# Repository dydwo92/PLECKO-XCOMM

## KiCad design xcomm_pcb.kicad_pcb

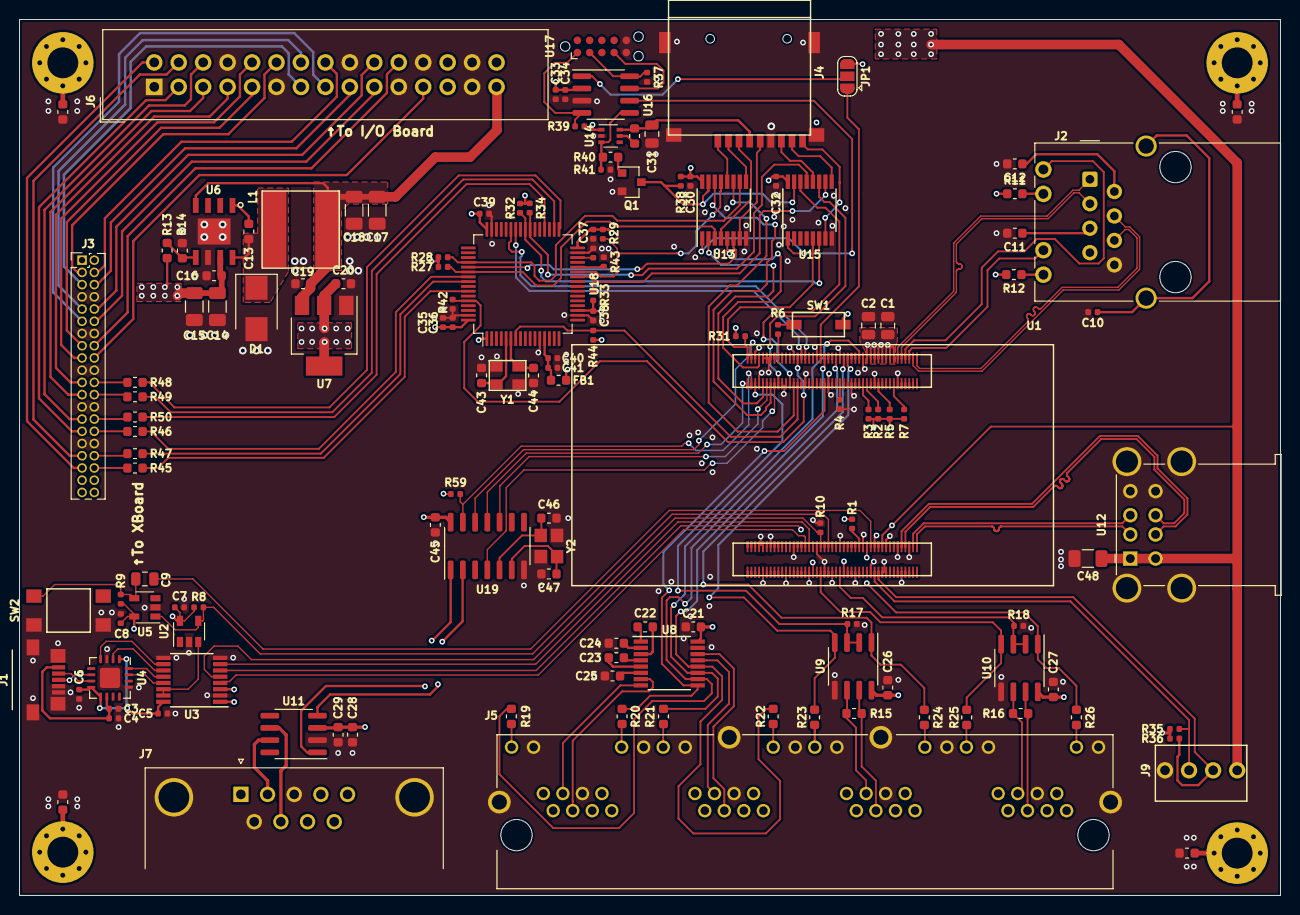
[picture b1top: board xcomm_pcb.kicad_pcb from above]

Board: 4 copper layers, 131.0 x 91.0 mm, 143 parts (0 on the bottom side), 166 nets.

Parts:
C1, C2, C9, C31: 10uF; C_0805_2012Metric
C3, C5, C6, C10, C30, C32, C34, C36, C37, C38, C39, C40: 100nF; C_0402_1005Metric
C4, C33, C35, C42: 4.7uF; C_0402_1005Metric
C7, C8, C41: 1uF; C_0402_1005Metric
C11, C12, C13, C21, C22, C26, C27, C29, C45: 100nF; C_0603_1608Metric
C14, C15: 10uF; C_1206_3216Metric
C16, C19, C20, C28: 1uF; C_0603_1608Metric
C17, C18: 47uF; C_1206_3216Metric
C23, C24, C25: 470nF; C_0603_1608Metric
C43, C44: 4pF; C_0603_1608Metric
C46, C47: 18pF; C_0603_1608Metric
C48: C; C_1206_3216Metric
D1: D_Schottky_ALT; D_SMB
FB1: Ferrite_Bead; L_0603_1608Metric
H1, H2, H3, H4: MountingHole_Pad; MountingHole_3.2mm_M3_Pad_Via
J1: USB_B_Micro; 0473461001
J2: Wuerth_7499010121A; RJ45_Wuerth_7499010121A_Horizontal
J3: EHF-120-01-L-D
J4: Micro_SD_Card; SD_Card_Socket
J5: RJHSE-5381-04; AMPHENOL_RJHSE538004
J6: Conn_02x15_Odd_Even; IDC-Header_2x15_P2.54mm_Vertical
J7: DB9_Male_MountingHoles; DSUB-9_Male_Horizontal_P2.77x2.84mm_EdgePinOffset4.94mm_Hou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
J9: Conn_01x04; 5045-04
JP1: SolderJumper_3_Open; SolderJumper-3_P1.3mm_Open_RoundedPad1.0x1.5mm
L1: 33uH; SRN8040-330M
Q1: BSS138; SOT-23
R1, R2, R3, R4, R5, R6, R7, R8, R9, R10, R27, R28, R29, R31, R32, R33, R34, R37, R38, R39, R41, R42, R43, R44, R59: 10k; R_0402_1005Metric
R11, R12, R19, R20, R21, R22, R23, R24, R25, R26: R; R_0603_1608Metric
R13: 68k; R_0603_1608Metric
R14: 20k; R_0603_1608Metric
R15, R16: 120; R_0603_1608Metric
R17, R18, R35, R36: R; R_0402_1005Metric
R30: 600; R_0603_1608Metric
R40, R45, R46, R47, R48, R49, R50: 100; R_0603_1608Metric
R51, R53, R56, R58: 0; R_0603_1608Metric
SW1: SW_DIP_x01; CHS-01TA
SW2: SW_Push; TACT_SWITCH
U1: DART-6UL
U2, U5: MIC2775; SOT-23-5
U3: SN74AVC4T245; TSSOP-16_4.4x5mm_P0.65mm
U4: FT230XQ; QFN-16-1EP_4x4mm_P0.65mm_EP2.1x2.1mm
U6: LM22675QMR-5.0; LM22675
U7: TLV1117-33; SOT-223-3_TabPin2
U8: MAX3232E; TSSOP-16_4.4x5mm_P0.65mm
U9, U10: THVD1450; SOIC-8_3.9x4.9mm_P1.27mm
U11: TCAN330; SOIC-8_3.9x4.9mm_P1.27mm
U12: 61400826021; USB_A_Wuerth_61400826021_Horizontal_Stacked
U13, U15: SN3257; TSSOP-16_4.4x5mm_P0.65mm
U14: TPS22919; SOT-363_SC-70-6
U16: STM32G030J6; SOIC-8_3.9x4.9mm_P1.27mm
U17: TAG_CONNECT; Tag-Connect_TC2050-IDC-NL_2x05_P1.27mm_Vertical
U18: STM32F446RETx; LQFP-64_10x10mm_P0.5mm
U19: MCP2518FDT-E/SL; SOIC-14_3.9x8.7mm_P1.27mm
Y1: 16MHz; ABM8
Y2: 20MHz; ABM8G

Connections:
/3V3: C1.1, C2.1, C7.1, C8.1, C20.2, C21.1, C26.1, C27.1, C28.1, C29.1, C30.2, C32.2, C33.1, C34.1, C35.1, C36.1, C37.1, C38.1, C39.1, C45.1, FB1.1, JP1.3, R1.1, R2.1, R3.1, R5.1, R7.1, R8.2, R9.2, R11.2, R12.2, R27.1, R28.1, R29.1, R31.1, R32.1, R33.1, R34.1, R35.1, R36.1, R38.1, R39.1, R44.2, R59.2, SW1.2, U1.A13, U1.A15, U1.A17, U1.A19, U1.A21, U1.A23, U1.A25, U1.A27, U1.B23, U2.5, U3.1, U3.3, U5.5, U7.2, U8.16, U9.8, U10.8, U11.3, U13.16, U14.1, U15.16, U16.2, U18.1, U18.19, U18.32, U18.48, U18.64, U19.14
/5V: C17.1, C18.1, C19.2, C48.1, J6.29, J6.30, J9.4, L1.2, U1.B19, U1.B40, U6.4, U7.3, U12.1, U12.5
/12V: C14.2, C15.2, C16.2, J3.1, J3.2, J6.25, J6.26, R13.1, U6.7
/Connectivity/CANH: J7.7, U11.6
/Connectivity/CANL: J7.2, U11.7
/Connectivity/CAN_RX: U11.4, U19.2
/Connectivity/CAN_TX: U11.1, U19.1
/Connectivity/I2C_SDA: J9.3, R36.2, U1.B22
/Connectivity/RS32_RX2_OUT: R22.1, U1.A43, U8.12
/Connectivity/RS232_RX1: J5.A6, U8.8
/Connectivity/RS232_RX1_OUT: R20.1, U1.A50, U8.9
/Connectivity/RS232_RX2: J5.B6, U8.13
/Connectivity/RS232_TX1: J5.A5, U8.7
/Connectivity/RS232_TX1_IN: R19.1, U1.A49, U8.10
/Connectivity/RS232_TX2: J5.B5, U8.14
/Connectivity/RS232_TX2_IN: R21.1, U1.A31, U8.11
/Connectivity/RS485_RX1: R24.1, U1.A39, U9.1
/Connectivity/RS485_RX2: R26.1, U1.B27, U10.1
/Connectivity/RS485_TXRX1+: J5.C6, R15.2, U9.6
/Connectivity/RS485_TXRX1-: J5.C5, R15.1, U9.7
/Connectivity/RS485_TXRX2+: J5.D6, R16.2, U10.6
/Connectivity/RS485_TXRX2-: J5.D5, R16.1, U10.7
/Connectivity/RX485_CTS1: R17.1, U1.A86, U9.2, U9.3
/Connectivity/RX485_CTS2: R18.1, U1.B42, U10.2, U10.3
/Connectivity/RX485_TX1: R23.1, U1.A37, U9.4
/Connectivity/RX485_TX2: R25.1, U1.B52, U10.4
/IO_G14: J3.17, J6.10
/IO_J15: J3.33, J6.4
/IO_J16: J3.35, J6.2
/IO_L14: J3.29, J6.3
/IO_L15: J3.27, J6.6
/IO_M14: J3.23, J6.5
/IO_M15: J3.21, J6.7
/IO_T5: J3.11, J6.15
/IO_U5: J3.9, J6.14
/IO_U8: J3.12, J6.19
/IO_U9: J3.10, J6.20
/IO_V7: J3.15, J6.9
/IO_V8: J3.4, J6.16
/IO_V10: J3.3, J6.12
/IO_V11: J3.5, J6.13
/IO_W8: J3.6, J6.17
/IO_Y8: J3.18, J6.23
/IO_Y9: J3.16, J6.22
/MCU/BOOT0: R42.2, U1.A63, U18.60
/MCU/SPI1_MISO: R47.1, U18.56
/MCU/SPI1_SCK: R46.1, U18.55
/MCU/SPI1_~CS: R45.1, U18.58
/MCU/SPI2_MOSI: R50.1, U18.36
/MCU/SPI2_SCK: R49.1, U18.34
/MCU/SPI2_~CS: R48.1, U18.33
/SD Card Swticher/3V3_SD: C31.1, J4.4, R30.1, U14.6
/SD Card Swticher/EN: R40.2, R41.1, U14.3, U16.5
/SD Card Swticher/MUX_SEL: U13.1, U15.1, U16.6
/SD Card Swticher/SD1_CMD: U1.A82, U13.2
/SD Card Swticher/SD1_DATA0: U1.A68, U15.14
/SD Card Swticher/SD1_DATA1: U1.A74, U15.11
/SD Card Swticher/SD1_DATA2: U1.A78, U13.14
/SD Card Swticher/SD1_DATA3: U1.A66, U13.11
/SD Card Swticher/SD1_SCK: U1.A83, U13.5
/SD Card Swticher/SD1_~DET: R31.2, U1.A89, U15.5
/SD Card Swticher/SD2_CMD: R27.2, U13.3, U18.54
/SD Card Swticher/SD2_DATA0: R34.2, U15.13, U18.39
/SD Card Swticher/SD2_DATA1: R33.2, U15.10, U18.26
/SD Card Swticher/SD2_DATA2: R29.2, U13.13, U18.27
/SD Card Swticher/SD2_DATA3: R28.2, U13.10, U18.52
/SD Card Swticher/SD2_SCK: U13.6, U18.53
/SD Card Swticher/SD2_~DET: R32.2, U15.6, U18.40
/SD Card Swticher/SD_CMD: J4.3, U13.4
/SD Card Swticher/SD_DATA0: J4.7, U15.12
/SD Card Swticher/SD_DATA1: J4.8, U15.9
/SD Card Swticher/SD_DATA2: J4.1, U13.12
/SD Card Swticher/SD_DATA3: J4.2, U13.9
/SD Card Swticher/SD_SCK: J4.5, U13.7
/SD Card Swticher/SD_~DET: J4.10, U15.7
/SD Card Swticher/SWCLK: R37.2, U16.8, U17.2
/SD Card Swticher/SWDIO: U16.7, U17.4
/SD Card Swticher/~EN: Q1.3, R38.2, U13.15, U15.15
/SD Card Swticher/~RST: R39.2, U16.4, U17.1
/SPI1_MISO: J3.34, R47.2
/SPI1_SCK: J3.30, R46.2
/SPI1_~CS: J3.36, R45.2
/SPI2_MOSI: J3.28, R50.2
/SPI2_SCK: J3.24, R49.2
/SPI2_~CS: J3.22, R48.2
/dart-6ul/3V3_OUT: C5.1, C6.1, U3.16, U4.1, U4.8, U4.9
/dart-6ul/BOOT1: R1.2, U1.B31
/dart-6ul/CAN_INT_B: U1.A76, U19.4
/dart-6ul/DEBUG_UART_CTS_B: U1.B57, U3.7
/dart-6ul/DEBUG_UART_EN: U2.3, U3.14, U3.15
/dart-6ul/DEBUG_UART_RTS_B: R10.2, U1.B51, U3.5
/dart-6ul/DEBUG_UART_RX: U1.B59, U3.4
/dart-6ul/DEBUG_UART_TX: U1.B56, U3.6
/dart-6ul/ECSPI2_MISO: U1.A87, U19.12
/dart-6ul/ECSPI2_MOSI: U1.A90, U19.11
/dart-6ul/ECSPI2_SCLK: U1.A80, U19.10
/dart-6ul/ECSPI2_SS0: R59.1, U1.A88, U19.13
/dart-6ul/ETH_RXDN: J2.6, U1.A1
/dart-6ul/ETH_RXDP: J2.4, U1.A3
/dart-6ul/ETH_TXDN: J2.3, U1.A9
/dart-6ul/ETH_TXDP: J2.1, U1.A11
/dart-6ul/GPIO4_18: R44.1, U1.A64, U18.7
/dart-6ul/GPIO5_5: JP1.1, U1.A51
/dart-6ul/I2C1_SCL: J9.2, R35.2, U1.B24
/dart-6ul/LCD_DATA5: R2.2, U1.A28
/dart-6ul/LCD_DATA6: R3.2, U1.A30
/dart-6ul/LCD_DATA7: R4.2, U1.A42
/dart-6ul/LCD_DATA9: R5.2, U1.A22
/dart-6ul/LCD_DATA11: R6.2, U1.A73
/dart-6ul/LCD_DATA13: R7.2, U1.A14
/dart-6ul/LINKLED: J2.9, U1.A7
/dart-6ul/LINKSPEED: J2.11, U1.A5
/dart-6ul/POR: R8.1, U1.B47, U2.4, U5.1
/dart-6ul/UART3_RX: U1.A61, U18.42
/dart-6ul/UART3_TX: U1.A59, U18.43
/dart-6ul/USB_DEBUG_N: J1.2, U4.7
/dart-6ul/USB_DEBUG_P: J1.3, U4.6
/dart-6ul/USB_OTG1_DN: U1.B1, U12.2
/dart-6ul/USB_OTG1_DP: U1.B3, U12.3
/dart-6ul/USB_OTG2_DN: U1.B9, U12.6
/dart-6ul/USB_OTG2_DP: U1.B7, U12.7
/dart-6ul/WDOG1_B: C9.2, U1.B25
GND: C1.2, C2.2, C3.2, C4.2, C5.2, C6.2, C7.2, C8.2, C10.1, C11.2, C12.2, C14.1, C15.1, C16.1, C17.2, C18.2, C19.1, C20.1, C21.2, C24.2, C25.2, C26.2, C27.2, C28.2, C29.2, C30.1, C31.2, C32.1, C33.2, C34.2, C35.2, C36.2, C37.2, C38.2, C39.2, C40.2, C41.2, C42.2, C43.2, C44.2, C45.2, C46.2, C47.2, C48.2, D1.2, J1.4, J1.5, J1.6, J2.8, J3.7, J3.8, J3.13, J3.14, J3.19, J3.20, J3.25, J3.26, J3.31, J3.32, J4.6, J4.9, J5.A4, J5.A9, J5.A11, J5.B4, J5.B9, J5.B11, J5.C4, J5.C9, J5.C11, J5.D4, J5.D9, J5.D11, J5.P$1, J5.P$2, J5.P$3, J5.P$4, J6.1, J6.8, J6.11, J6.18, J6.21, J6.24, J6.27, J6.28, J7.0, J7.3, J7.6, J9.1, Q1.2, R4.1, R10.1, R14.2, R17.2, R18.2, R37.1, R41.2, R42.1, R43.2, R51.2, R53.2, R56.2, R58.2, SW2.1, SW2.2, U1.A12, U1.A24, U1.A29, U1.A36, U1.A41, U1.A48, U1.A53, U1.A60, U1.A65, U1.A70, U1.A72, U1.A77, U1.A79, U1.A81, U1.A84, U1.A85, U1.B5, U1.B10, U1.B11, U1.B17, U1.B18, U1.B20, U1.B26, U1.B29, U1.B34, U1.B41, U1.B46, U1.B50, U1.B53, U1.B58, U1.B65, U1.B70, U1.B77, U1.B81, U1.B82, U1.B83, U2.2, U3.2, U3.8, U3.9, U4.3, U4.13, U4.17, U5.2, U6.6, U6.9, U7.1, U8.15, U9.5, U10.5, U11.2, U12.4, U12.8, U12.9, U13.8, U14.2, U15.8, U16.3, U17.5, U17.6, U18.12, U18.18, U18.31, U18.47, U18.63, U19.7, Y1.2, Y1.4, Y2.2, Y2.4
unnamed: C3.1, C4.1, J1.1, U4.10
unnamed: C9.1, R9.1, SW2.3, U5.4
unnamed: C10.2, J2.SH
unnamed: C11.1, J2.5
unnamed: C12.1, J2.2
unnamed: C13.1, D1.1, L1.1, U6.8
unnamed: C13.2, U6.1
unnamed: C22.1, U8.1
unnamed: C22.2, U8.3
unnamed: C23.1, U8.4
unnamed: C23.2, U8.5
unnamed: C24.1, U8.2
unnamed: C25.1, U8.6
unnamed: C40.1, C41.1, FB1.2, U18.13
unnamed: C42.1, U18.30
unnamed: C43.1, U18.5, Y1.1
unnamed: C44.1, U18.6, Y1.3
unnamed: C46.1, U19.5, Y2.3
unnamed: C47.1, U19.6, Y2.1
unnamed: H1.1, R51.1
unnamed: H2.1, R53.1
unnamed: H3.1, R56.1
unnamed: H4.1, R58.1
unnamed: J2.10, R11.1
unnamed: J2.12, R12.1
unnamed: J5.A10, R20.2
unnamed: J5.A12, R19.2
unnamed: J5.B10, R22.2
unnamed: J5.B12, R21.2
unnamed: J5.C10, R24.2
unnamed: J5.C12, R23.2
unnamed: J5.D10, R26.2
unnamed: J5.D12, R25.2
unnamed: JP1.2, U16.1
unnamed: Q1.1, R40.1
unnamed: R6.1, SW1.1
unnamed: R13.2, R14.1, U6.5
unnamed: R30.2, U14.5
unnamed: R43.1, U18.28
unnamed: U3.10, U4.4
unnamed: U3.11, U4.2
unnamed: U3.12, U4.16
unnamed: U3.13, U4.15

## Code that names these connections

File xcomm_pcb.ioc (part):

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Mcu.UserName=STM32F446RETx
PC11.Signal=SDIO_D3
PC12.Signal=SDIO_CK
PC8.Signal=SDIO_D0
PB13.Signal=SPI2_SCK
PB15.Signal=SPI2_MOSI
PA9.Signal=USART1_TX
PB6.Signal=GPIO_Output
PB14.Signal=SPI2_MISO
PD2.Mode=SD_4_bits_Wide_bus
PC12.Mode=SD_4_bits_Wide_bus
PB0.Mode=SD_4_bits_Wide_bus
board=custom
Mcu.Name=STM32F446R(C-E)Tx
PC8.Mode=SD_4_bits_Wide_bus
PB3.Signal=SPI1_SCK
Mcu.Package=LQFP64
PB5.Signal=SPI1_MOSI
PB1.Signal=SDIO_D2
PA10.Signal=USART1_RX
PB1.Mode=SD_4_bits_Wide_bus
PC11.Mode=SD_4_bits_Wide_bus
PC9.Signal=GPIO_Input
PD2.Signal=SDIO_CMD
PB0.Signal=SDIO_D1
PB12.Signal=SPI2_NSS
PB4.Signal=SPI1_MISO
